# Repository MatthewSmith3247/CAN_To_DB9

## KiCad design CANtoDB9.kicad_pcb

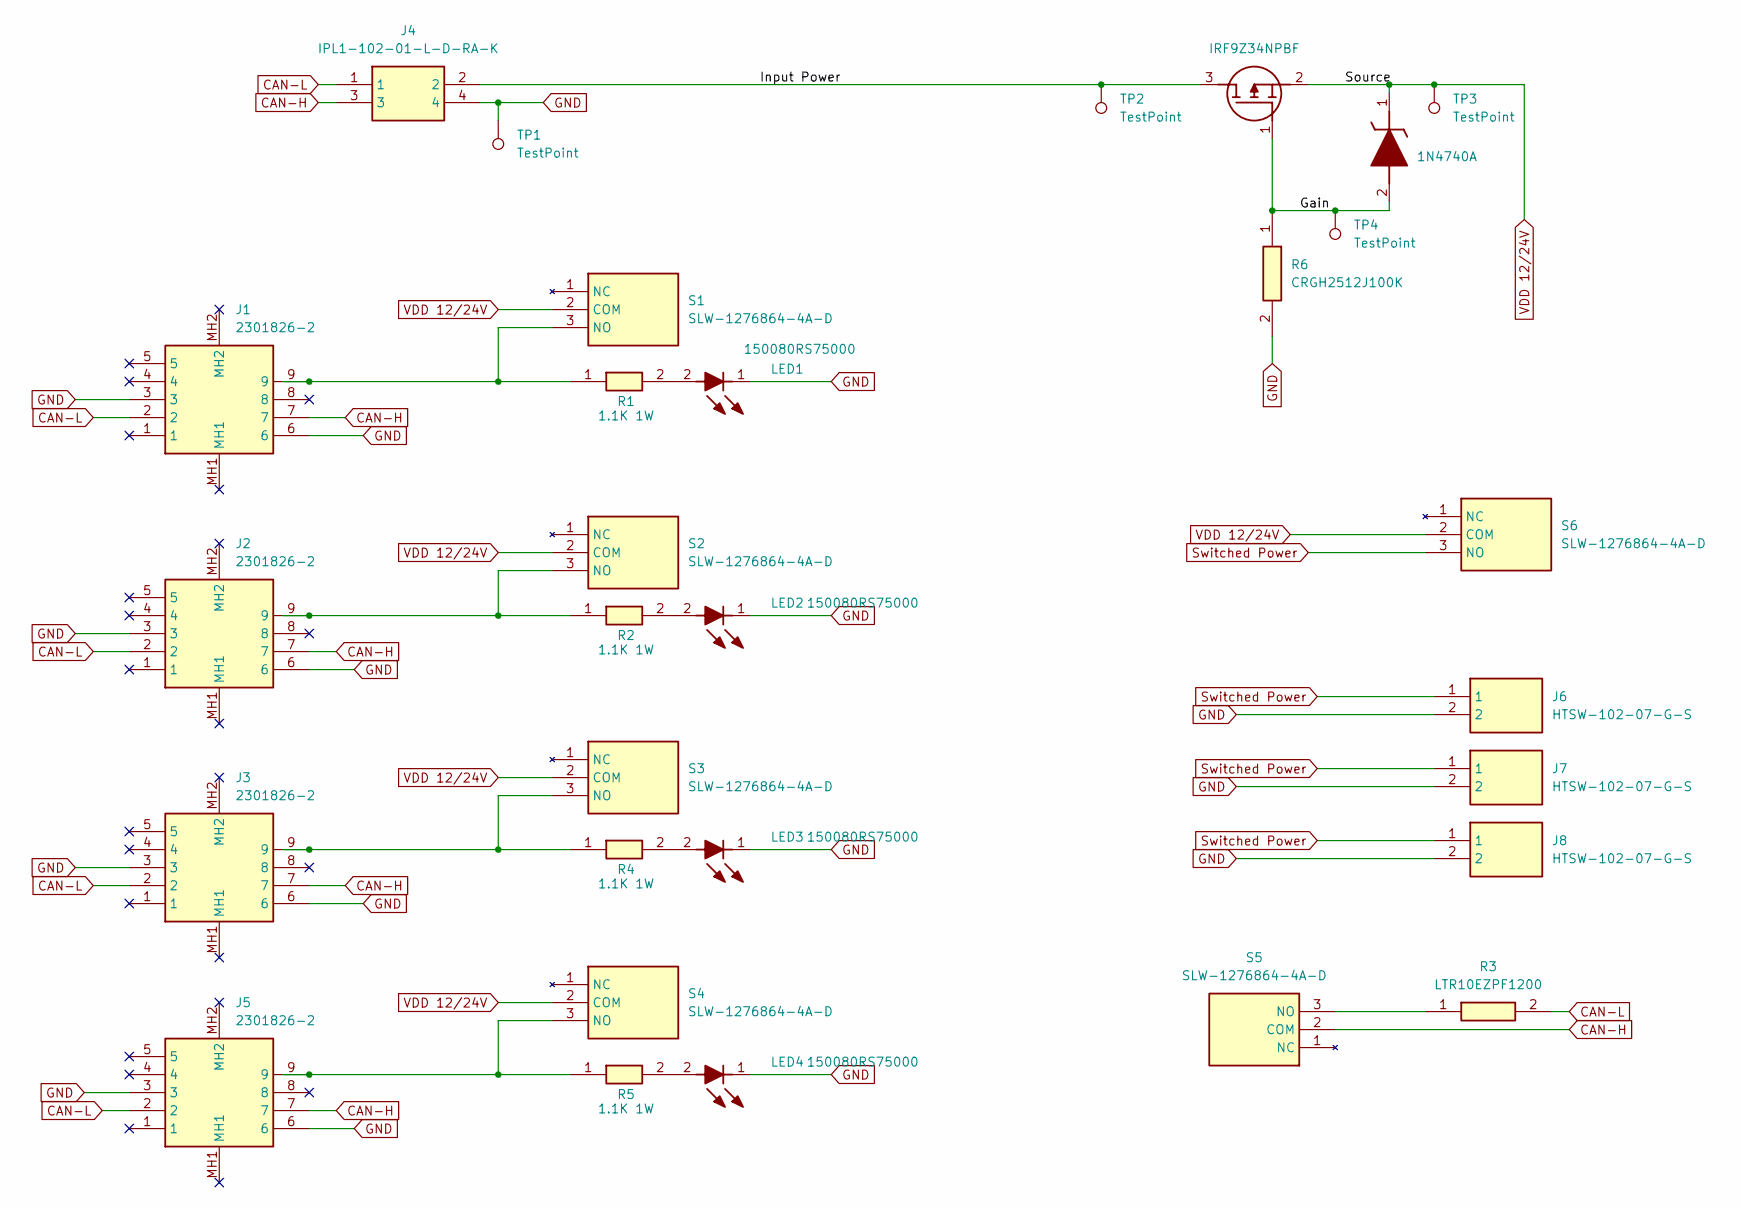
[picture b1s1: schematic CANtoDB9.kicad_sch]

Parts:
J1, J2, J3, J5: 2301826-2; 23018262; Mouser Part Number 571-2301826-2
J4: IPL1-102-01-L-D-RA-K; IPL1-102-01-YYY-D-RA-K; Mouser Part Number 200-IPL110201LDRAK
J6, J7, J8: HTSW-102-07-G-S; HDRV2W64P0X254_1X2_508X248X838P; Mouser Part Number 200-HTSW10207GS
LED1, LED2, LED3, LED4: 150080RS75000; LEDC2012X80N; Mouser Part Number 710-150080RS75000
Q1: IRF9Z34NPBF; TO254P469X1042X1967-3P; Mouser Part Number 942-IRF9Z34NPBF
R1, R2, R4, R5: 1.1K 1W; ERJS1T_U1T__2512_; Mouser Part Number 667-ERJ-U1TF1101U
R3: LTR10EZPF1200; RESC1220X65N; Mouser Part Number 755-LTR10EZPF1200
R6: CRGH2512J100K; RESC6432X65N; Mouser Part Number 279-CRGH2512J100K
S1, S2, S3, S4, S5, S6: SLW-1276864-4A-D; SLW12768644AD; Mouser Part Number 179-SLW-1276864-4A-D
TP1, TP2, TP3, TP4: TestPoint; TestPoint_Pad_D2.0mm
Z1: 1N4740A; DIOAD1570W85L450D280; Mouser Part Number 512-1N4740A

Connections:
/Gain: Q1.1 (G), R6.1, TP4.1, Z1.2 (A)
/Input Power: J4.2, Q1.3 (D), TP2.1
CAN-H: J1.7, J2.7, J3.7, J4.3, J5.7, S5.2 (COM); also elsewhere on the board
CAN-L: J1.2, J2.2, J3.2, J4.1, J5.2, R3.2; also elsewhere on the board
GND: J1.3, J1.6, J2.3, J2.6, J3.3, J3.6, J4.4, J5.3, J5.6, J6.2, J7.2, J8.2, LED1.1 (K), LED2.1 (K), LED3.1 (K), LED4.1 (K), R6.2, TP1.1; also elsewhere on the board
unnamed: LED1.2 (A), R1.2
unnamed: LED2.2 (A), R2.2
unnamed: LED3.2 (A), R4.2
unnamed: LED4.2 (A), R5.2
unnamed 9: J1.9, R1.1, S1.3 (NO); also elsewhere on the board
unnamed: J2.9, R2.1, S2.3 (NO)
unnamed 11: J3.9, R4.1, S3.3 (NO); also elsewhere on the board
unnamed 12: J5.9, R5.1, S4.3 (NO); also elsewhere on the board
unnamed: R3.1, S5.3 (NO)
Switched Power: J6.1, J7.1, J8.1, S6.3 (NO)
VDD 12/24V: Q1.2 (S), S1.2 (COM), S2.2 (COM), S3.2 (COM), S4.2 (COM), S6.2 (COM), TP3.1, Z1.1 (K)

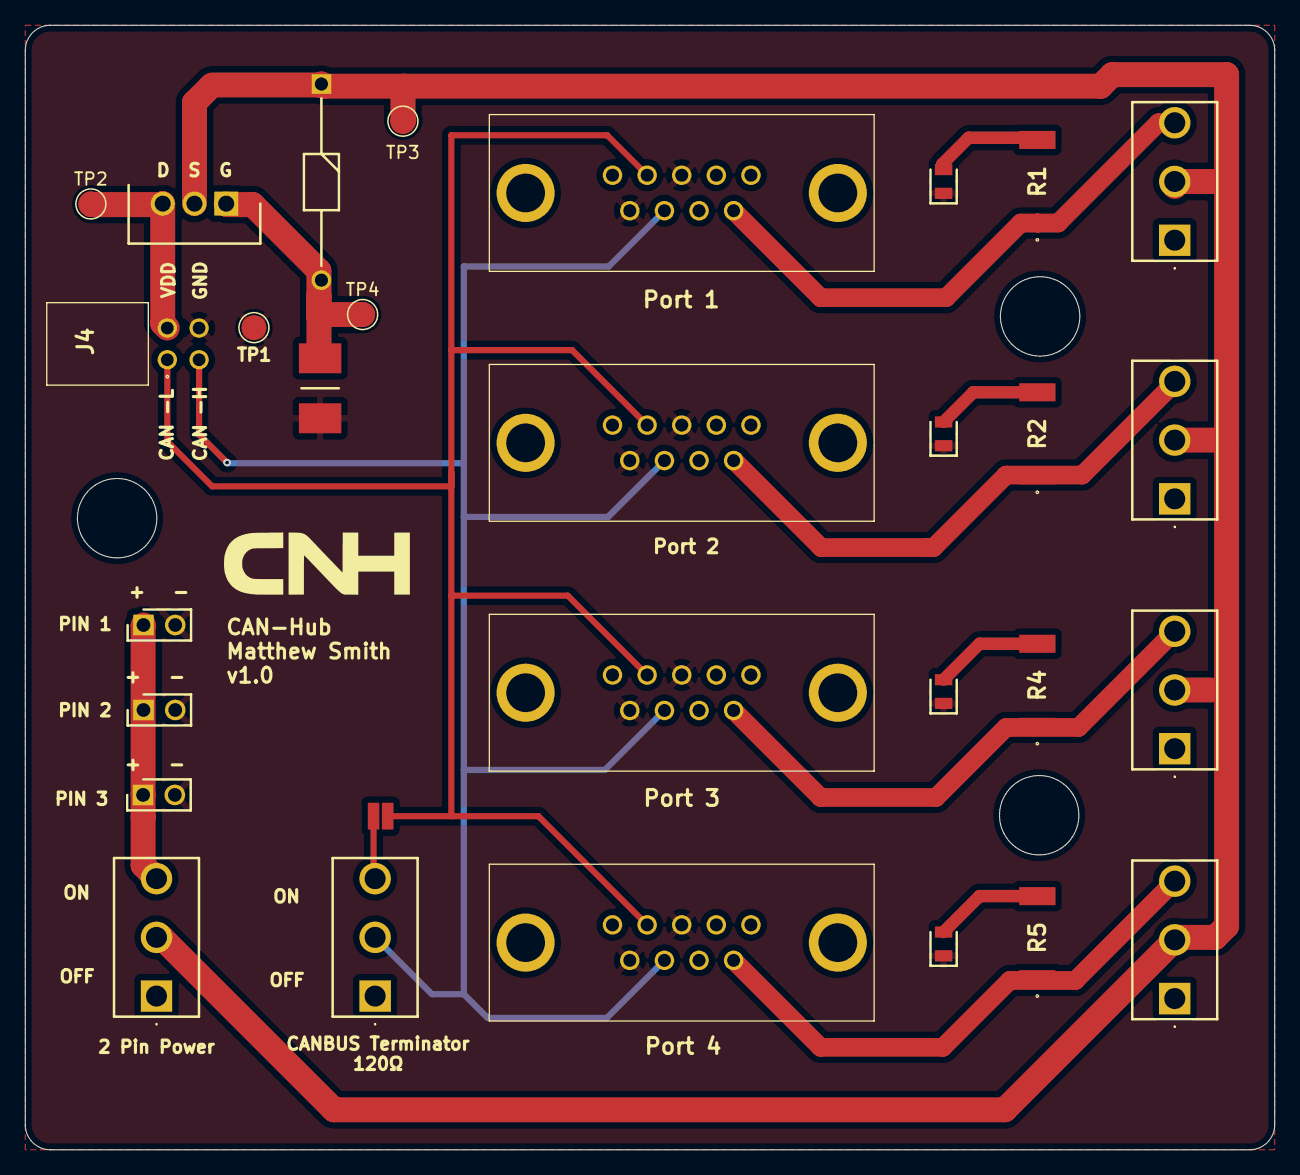
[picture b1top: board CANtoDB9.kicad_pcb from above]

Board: 2 copper layers, 100.0 x 90.0 mm, 30 parts (0 on the bottom side), 16 nets.

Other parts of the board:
Port 1, Port 3, Port 4: 2301826-2; 23018262

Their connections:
CAN-H: Port 1.7, Port 3.7, Port 4.7; also elsewhere on the board
CAN-L: Port 1.2, Port 3.2, Port 4.2; also elsewhere on the board
GND: Port 1.3, Port 1.6, Port 3.3, Port 3.6, Port 4.3, Port 4.6; also elsewhere on the board
unnamed 9: Port 1.9; also elsewhere on the board
unnamed 11: Port 3.9; also elsewhere on the board
unnamed 12: Port 4.9; also elsewhere on the board
